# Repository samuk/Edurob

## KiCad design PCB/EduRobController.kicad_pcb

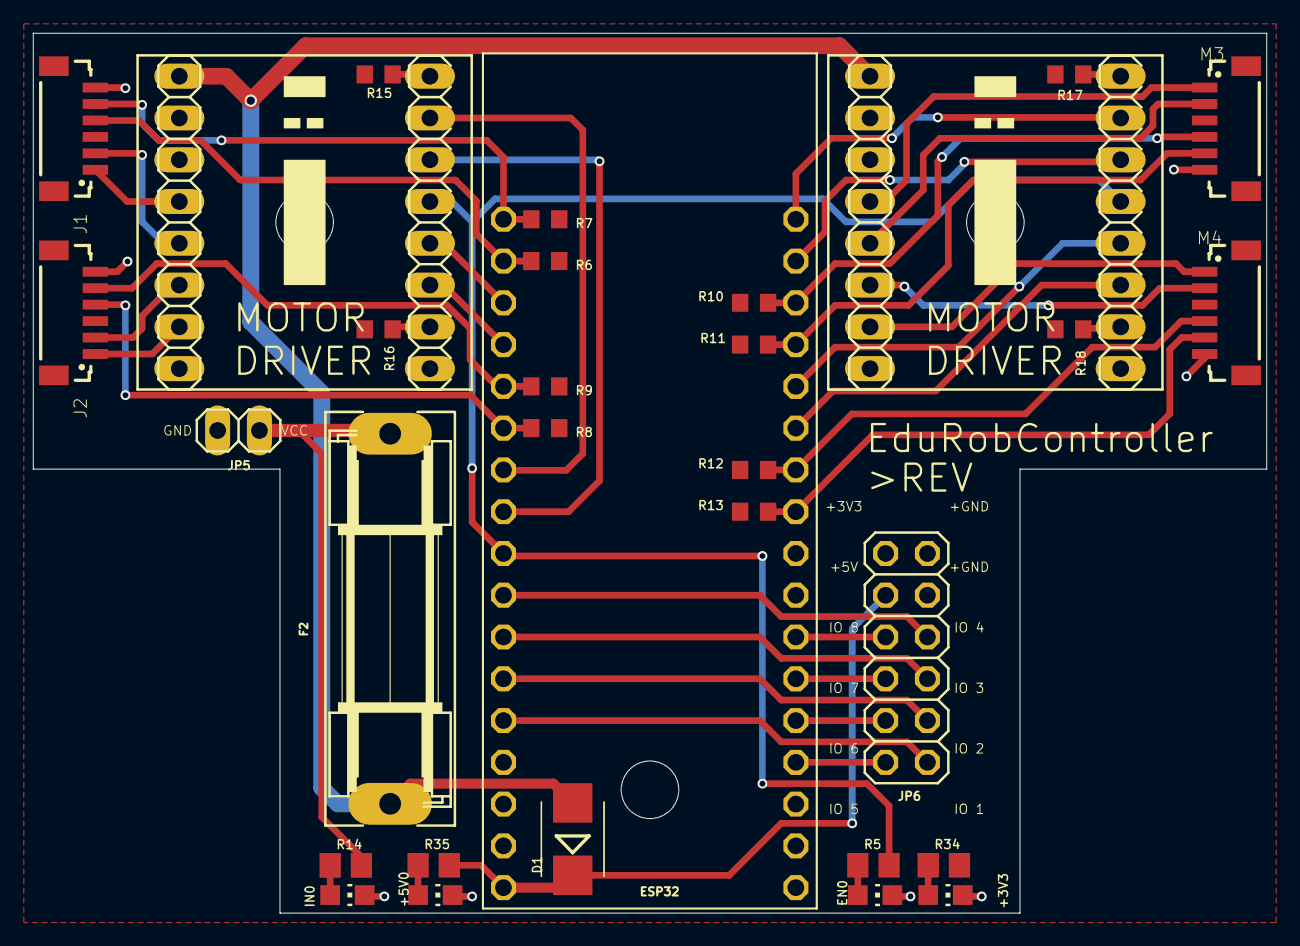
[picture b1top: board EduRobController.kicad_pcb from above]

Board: 2 copper layers, 75.0 x 53.5 mm, 34 parts (0 on the bottom side), 46 nets.

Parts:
+3V3, +5V0: CHIP-LED0805
@HOLE0, @HOLE1, @HOLE2: (no value)
D1: SMB
EN0: CHIP-LED0805
F2: 534-4628; SH22,5
IN0: CHIP-LED0805
J1, J2: 665306124022
JP5: 1X02
JP6: 2X06
M3, M4: 665306124022
R5, R14, R34, R35: R0805
R6, R7, R8, R9, R10, R11, R12, R13, R15, R16, R17, R18: R0603
U$1: ESP32
U$2, U$3: TB6612FNG; 2X08

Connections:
+3V3: J1.3, J2.3, JP6.12, M3.3, M4.3, R6.2, R7.2, R8.2, R9.2, R10.2, R11.2, R12.2, R13.2, R15.2, R16.2, R17.2, R18.2, R34.2, U$1.3V3, U$1.3V3., U$2.7, U$3.7
+5V: D1.C, JP6.10, R35.2, U$1.5V
ENM: R5.2, U$1.12, U$2.13, U$3.13
GND: +3V3.C, +5V0.C, EN0.C, IN0.C, J1.6, J2.6, JP5.2, JP6.9, JP6.11, M3.6, M4.6, U$1.GND, U$1.GND., U$2.1, U$2.6, U$2.9, U$3.1, U$3.6, U$3.9
GPIO1: JP6.1, U$1.4
GPIO2: JP6.3, U$1.2
GPIO3: JP6.5, U$1.15
GPIO4: JP6.7, U$1.13
GPIO5: JP6.2, U$1.37
GPIO6: JP6.4, U$1.38
GPIO7: JP6.6, U$1.34
GPIO8: JP6.8, U$1.35
M1A: J1.1, U$2.5
M1B: J1.2, U$2.4
M1ENCA: J1.4, R6.1, U$1.VN
M1ENCB: J1.5, R7.1, U$1.VP
M1PWMA: U$1.14, U$2.14
M1PWMB: U$1.27, U$2.15
M2A: J2.1, U$2.2
M2B: J2.2, U$2.3
M2ENCA: J2.4, R8.1, U$1.33
M2ENCB: J2.5, R9.1, U$1.32
M2PWMA: U$1.25, U$2.12
M2PWMB: U$1.26, U$2.11
M3A: M3.1, U$3.5
M3B: M3.2, U$3.4
M3ENCA: M3.4, R10.1, U$1.19
M3ENCB: M3.5, R11.1, U$1.23
M3PWMA: U$1.22, U$3.14
M3PWMB: U$1.21, U$3.15
M4A: M4.1, U$3.2
M4B: M4.2, U$3.3
M4ENCA: M4.4, R12.1, U$1.10
M4ENCB: M4.5, R13.1, U$1.9
M4PWMA: U$1.18, U$3.12
M4PWMB: U$1.5, U$3.11
unnamed: +3V3.A, R34.1
unnamed: +5V0.A, R35.1
unnamed: EN0.A, R5.1
unnamed: IN0.A, R14.1
unnamed: R17.1, U$3.16
unnamed: R18.1, U$3.10
unnamed: R15.1, U$2.16
unnamed: R16.1, U$2.10
VCC: F2.1, JP5.1, R14.2
VDD: D1.A, F2.2, U$2.8, U$3.8

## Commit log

2023-05-27 Kicad 7 version
